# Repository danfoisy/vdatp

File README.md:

# VDATP
## Volumetric Display using an Acoustically Trapped Particle

This was such a fun project - I still giggle (maniacally) when watching this thing go.  There's something truly magical about watching something levitate in mid-air and then start zipping around so fast, you can't see it.  In any case, I hope these project files help someone!

Video: https://www.youtube.com/watch?v=hCC1C5KIeUA

References:
- PhysicsGirl acoustic levitator: https://www.youtube.com/watch?v=ABjRnSYw-4k
- Acoustic levitator Instructable: https://www.instructables.com/Acoustic-Levitator/
- University of Sussex video: https://www.youtube.com/watch?v=Tm8JRlJ1q50
- University of Sussex paper: http://sro.sussex.ac.uk/id/eprint/86930/

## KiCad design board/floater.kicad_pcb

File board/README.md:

# Board

Herein lives the Kicad schedmatics, PCB and BOM files.  If looking to replicate, I highly recommend you look at `errata.txt` for a list of mistakes I made that should be fixed on the next spin of the board.

Some notes:
- SPI goes to all 4 FPGAs simultaneously.  MISO is not used
- there are jumpers in place to allow the board to operate with only one FPGA installed (and only 50 transducers) but to run both FPGAs, the following jumpers must be configured:
-- R122, R123, R124, R126, R127, R128 <= populated
-- R125, R129 <= not populated
-- R105, R111, R113 <= not populated
-- R112 <= populated
- Raspberry Pi W installed on top board only. Top board needs 5V DC/DC converter populated, leave unpopulated on bottom board
-- Rasberry Pi header soldered on backside of Pi 
- U101 and U102 are soldered on top board (note errata on U101). Only U101 populated on bottom board
-- only simple twisted pair required for each RS485 connection
- LEDs only connect on top board (populate LED drivers and connectors)
- each board requires a max of 2A at 24V. No power sequencing required
- to allow the config device to program the FPGAs
-- JP201/JP202 must be left unpopulated
-- JP11001/JP11002 must be cut and msel0/1 must be connected to ground with jumper
- each FPGA must have jumpers configured to tell it which transducers it is responsible for
-- top board: populate R11004
-- bottom board: populate R11003, R203, R204
- original ultrasonic transducer is no available on aliexpress but https://manorshi.en.alibaba.com/product/60248714908-801018150/Manorshi_10mm_40khz_piezo_ultrasonic_Transmitter_Receiver_sensor.html should work but I've not tested (make sure to order the transmitter version)
- distance between boards is not super critical - mine are set up 145mm apart but other distance work just as well
- FPGAs can be programmed with a USB blaster type device.  I use https://www.terasic.com.tw/cgi-bin/page/archive.pl?Language=English&No=46
-- all FPGAs get the same program
- the transducers have a polarity marked on them - but don't trust the markings as they are wrong much of the time.  As well, I've been informed that there are phase discrepancies inherent in most of these cheap transducers.  I corrected for polarity errors by testing each transducer individually but did not correct for phase errors - this may be the cause of some of the distortions I saw.  I did check for these phase discrepancies and found a maximum of about 3% phase error across the transducers.  I don't know if this is enough to cause serious distortions but it may be worthwhile for someone to investigate.  If this is of concern, a simple LUT can be implemented to compensate for these errors on a transducer by transducer basis
- running these boards at 15V causes the drivers to get really hot - I suggest running them at 10V.

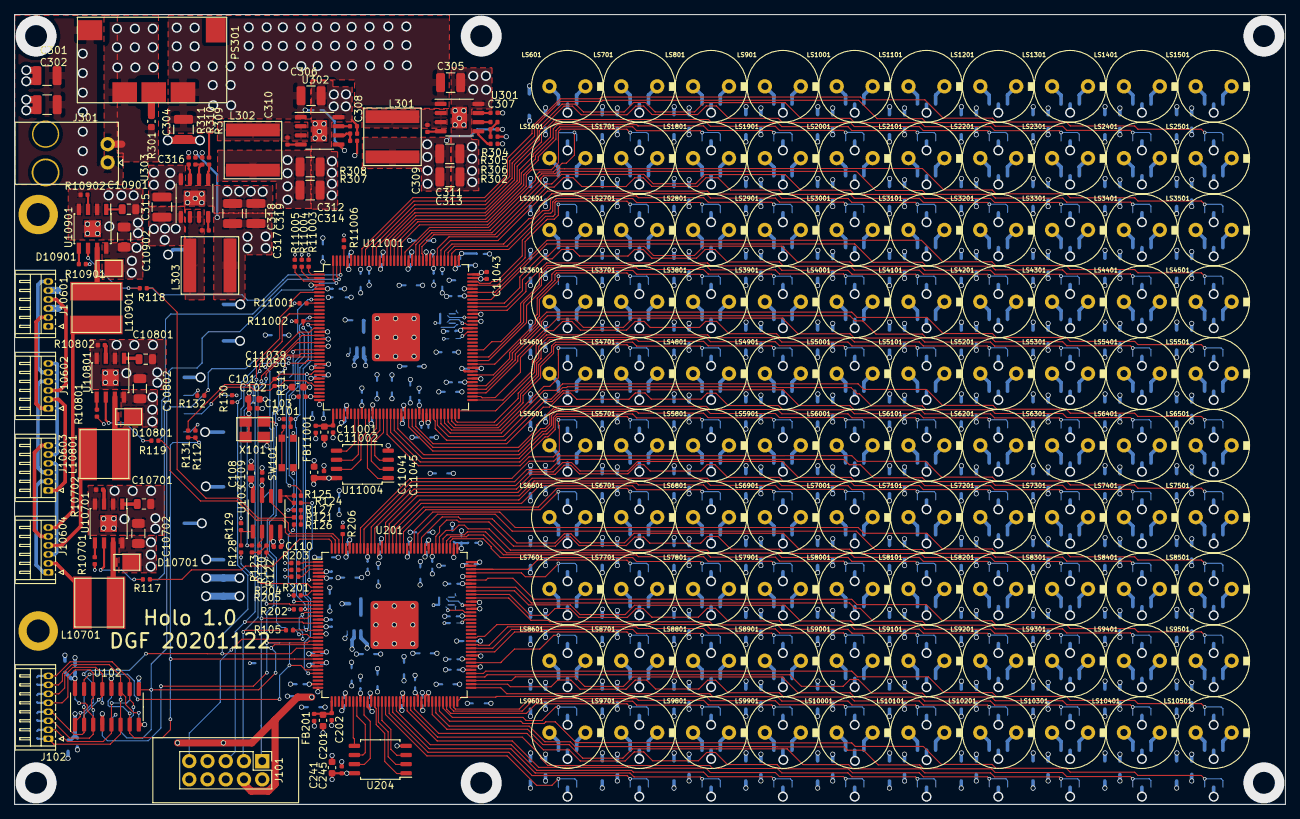
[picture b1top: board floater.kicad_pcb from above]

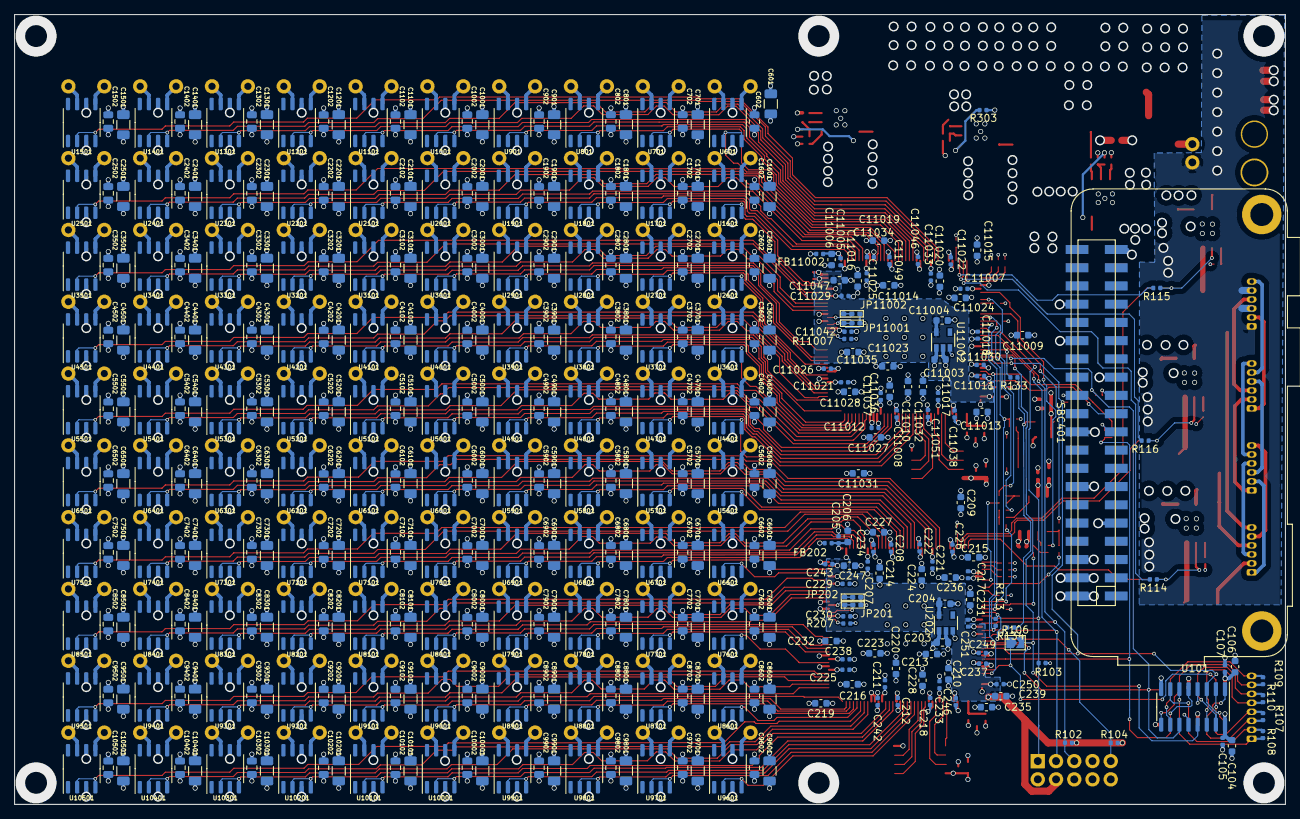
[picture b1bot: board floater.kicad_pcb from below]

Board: 4 copper layers, 177.0 x 110.0 mm, 638 parts (416 on the bottom side), 432 nets.

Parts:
C101, C104, C106, C108, C201, C203, C204, C206, C209, C210, C213, C214, C215, C216, C219, C220, C223, C224, C227, C228, C231, C232, C235, C236, C239, C241, C247, C11001, C11003, C11004, C11006, C11009, C11010, C11013, C11014, C11015, C11016, C11019, C11020, C11023, C11024, C11027, C11028, C11031, C11032, C11035, C11036, C11039, C11041, C11047: 4.7uF; C_0603_1608Metric
C102, C103, C105, C107, C109, C110, C202, C205, C207, C208, C211, C212, C217, C218, C221, C222, C225, C226, C229, C230, C233, C234, C237, C238, C242, C243, C245, C246, C249, C250, C251, C307, C308, C309, C310, C316, C317, C11002, C11005, C11007, C11008, C11011, C11012, C11017, C11018, C11021, C11022, C11025, C11026, C11029, C11030, C11033, C11034, C11037, C11038, C11042, C11043, C11045, C11046, C11049, C11050, C11051: 0.1uF; C_0402_1005Metric
C301, C302: 10uF,50V; R_1210_3225Metric
C304, C305, C306, C315: 22uF,35V; C_1210_3225Metric
C311, C312, C313, C314, C318, C319: 22uF; C_1210_3225Metric
C601, C701, C801, C901, C1001, C1101, C1201, C1301, C1401, C1501, C1601, C1701, C1801, C1901, C2001, C2101, C2201, C2301, C2401, C2501, C2601, C2701, C2801, C2901, C3001, C3101, C3201, C3301, C3401, C3501, C3601, C3701, C3801, C3901, C4001, C4101, C4201, C4301, C4401, C4501, C4601, C4701, C4801, C4901, C5001, C5101, C5201, C5301, C5401, C5501, C5601, C5701, C5801, C5901, C6001, C6101, C6201, C6301, C6401, C6501, C6601, C6701, C6801, C6901, C7001, C7101, C7201, C7301, C7401, C7501, C7601, C7701, C7801, C7901, C8001, C8101, C8201, C8301, C8401, C8501, C8601, C8701, C8801, C8901, C9001, C9101, C9201, C9301, C9401, C9501, C9601, C9701, C9801, C9901, C10001, C10101, C10201, C10301, C10401, C10501, C10702, C10802, C10902: 4.7uF, 35V; C_1206_3216Metric
C602, C702, C802, C902, C1002, C1102, C1202, C1302, C1402, C1502, C1602, C1702, C1802, C1902, C2002, C2102, C2202, C2302, C2402, C2502, C2602, C2702, C2802, C2902, C3002, C3102, C3202, C3302, C3402, C3502, C3602, C3702, C3802, C3902, C4002, C4102, C4202, C4302, C4402, C4502, C4602, C4702, C4802, C4902, C5002, C5102, C5202, C5302, C5402, C5502, C5602, C5702, C5802, C5902, C6002, C6102, C6202, C6302, C6402, C6502, C6602, C6702, C6802, C6902, C7002, C7102, C7202, C7302, C7402, C7502, C7602, C7702, C7802, C7902, C8002, C8102, C8202, C8302, C8402, C8502, C8602, C8702, C8802, C8902, C9002, C9102, C9202, C9302, C9402, C9502, C9602, C9702, C9802, C9902, C10002, C10102, C10202, C10302, C10402, C10502: 0.1uF, 35V; C_0805_2012Metric
C10701, C10801, C10901: 1uF, 16V; C_0805_2012Metric
D10701, D10801, D10901: 2A, 100V; DO-220A
FB201, FB202, FB11001, FB11002: 300R; R_0402_1005Metric
J101: JTAG; PinHeader_2x05_P2.54mm_Vertical_Shrouded
J102: Comms; Hirose_DF13-08P-1.25DS_1x08_P1.25mm_Horizontal
J301: Power; Molex_70555_RA_1x02_P2.54
J10601, J10602, J10603, J10604: Screw_Terminal_01x06; Hirose_DF13-06P-1.25DS_1x06_P1.25mm_Horizontal
JP201, JP202, JP11001, JP11002: SolderJumper_3_Bridged12; SolderJumper-3_bridged12
L301: 2.0uH; NR8040
L302: 3.6uH; NR8040
L303: 4.7uH; NR8040
L10701, L10801, L10901: 11.5uH; SRR6038
LS601, LS701, LS801, LS901, LS1001, LS1101, LS1201, LS1301, LS1401, LS1501, LS1601, LS1701, LS1801, LS1901, LS2001, LS2101, LS2201, LS2301, LS2401, LS2501, LS2601, LS2701, LS2801, LS2901, LS3001, LS3101, LS3201, LS3301, LS3401, LS3501, LS3601, LS3701, LS3801, LS3901, LS4001, LS4101, LS4201, LS4301, LS4401, LS4501, LS4601, LS4701, LS4801, LS4901, LS5001, LS5101, LS5201, LS5301, LS5401, LS5501, LS5601, LS5701, LS5801, LS5901, LS6001, LS6101, LS6201, LS6301, LS6401, LS6501, LS6601, LS6701, LS6801, LS6901, LS7001, LS7101, LS7201, LS7301, LS7401, LS7501, LS7601, LS7701, LS7801, LS7901, LS8001, LS8101, LS8201, LS8301, LS8401, LS8501, LS8601, LS8701, LS8801, LS8901, LS9001, LS9101, LS9201, LS9301, LS9401, LS9501, LS9601, LS9701, LS9801, LS9901, LS10001, LS10101, LS10201, LS10301, LS10401, LS10501: Speaker_Ultrasound; MSO-P1040H07T
PS301: OKI-T36W-W40; OKI-T-36W-W40
R101: 330R; R_0402_1005Metric
R102, R104, R201, R202, R203, R204, R205, R206, R207, R11001, R11002, R11003, R11004, R11005, R11006, R11007: 10K; R_0402_1005Metric
R103: 1.0K; R_0402_1005Metric
R105, R111, R112, R113, R114, R115, R116, R117, R118, R119: 0R; R_0402_1005Metric
R106: 0R; SolderJumper-2_P1.3mm_Open_TrianglePad1.0x1.5mm
R107, R108, R109, R110, R130, R131, R132: 100R; R_0402_1005Metric
R120: 24R9; R_0402_1005Metric
R121: 50R; R_0402_1005Metric
R122, R123, R124, R125, R126, R127, R128, R129: SOT; R_0402_1005Metric
R133, R134: 25R; R_0402_1005Metric
R301: 52R21; R_0603_1608Metric
R302, R303, R309: 100K; R_0402_1005Metric
R304: 47K; R_0402_1005Metric
R305: 5.0K; R_0402_1005Metric
R306: 10.31K; R_0402_1005Metric
R307, R310: 75K; R_0402_1005Metric
R308: 27.6K; R_0402_1005Metric
R311: 14.46K; R_0402_1005Metric
R10701, R10801, R10901: 20K; R_0402_1005Metric
R10702, R10802, R10902: 8.9K; R_0402_1005Metric
SBC401: Raspberry_Pi_2_3; Raspberry_Pi_Zero_Socketed_THT_MountingHoles_SMT
SW101: SW_Push; SW_SPST_KMR2
U101: AM26LV32CDR; SOIC-16_3.9x9.9mm_P1.27mm
U102: AM26LV31; SOIC-16_3.9x9.9mm_P1.27mm
U103: EPCQ16A; SOIC-8_3.9x4.9mm_P1.27mm
U201, U11001: 10CL010YE144C8G; EQFP-144-1EP_20x20mm_P0.5mm_EP6.7x6.7mm
U202, U11002: MIC5504-2.5YM5; SOT-23-5
U204, U11004: S25FL128L; SOIC-8_5.275x5.275mm_P1.27mm
U301, U302, U303: RT7263A; SOP-EP-8_3.9x4.9mm_P1.27mm
U601, U701, U801, U901, U1001, U1101, U1201, U1301, U1401, U1501, U1601, U1701, U1801, U1901, U2001, U2101, U2201, U2301, U2401, U2501, U2601, U2701, U2801, U2901, U3001, U3101, U3201, U3301, U3401, U3501, U3601, U3701, U3801, U3901, U4001, U4101, U4201, U4301, U4401, U4501, U4601, U4701, U4801, U4901, U5001, U5101, U5201, U5301, U5401, U5501, U5601, U5701, U5801, U5901, U6001, U6101, U6201, U6301, U6401, U6501, U6601, U6701, U6801, U6901, U7001, U7101, U7201, U7301, U7401, U7501, U7601, U7701, U7801, U7901, U8001, U8101, U8201, U8301, U8401, U8501, U8601, U8701, U8801, U8901, U9001, U9101, U9201, U9301, U9401, U9501, U9601, U9701, U9801, U9901, U10001, U10101, U10201, U10301, U10401, U10501: TC4428A; SO-8_3.9x4.9mm_P1.27mm
U10701, U10801, U10901: LM3414HV; SOIC-8-1EP_3.9x4.9mm_P1.27mm_EP2.35x2.35mm
X101: ASE-24.576MHz; ASFL1

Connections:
+1V2: C207.1, C210.1, C211.1, C214.1, C216.1, C217.1, C220.1, C221.1, C224.1, C225.1, C228.1, C229.1, C232.1, C233.1, C236.1, C237.1, C311.1, C313.1, C11007.1, C11010.1, C11011.1, C11014.1, C11016.1, C11017.1, C11020.1, C11021.1, C11024.1, C11025.1, C11028.1, C11029.1, C11032.1, C11033.1, C11036.1, C11037.1, FB201.1, FB202.1, FB11001.1, FB11002.1, L301.2, R305.1, U201.5, U201.29, U201.45, U201.61, U201.78, U201.102, U201.116, U201.134, U11001.5, U11001.29, U11001.45, U11001.61, U11001.78, U11001.102, U11001.116, U11001.134
+2V5: C204.1, C239.1, C243.1, C247.1, C250.1, J101.4, JP201.1, JP202.1, R102.2, R104.2, U201.35, U201.107, U202.5
+3V0: C101.1, C102.1, C104.1, C105.1, C106.1, C107.1, C108.1, C109.1, C110.1, C203.1, C208.1, C209.1, C212.1, C213.1, C215.1, C218.1, C219.1, C222.1, C223.1, C226.1, C227.1, C230.1, C231.1, C234.1, C235.1, C238.1, C241.1, C242.1, C245.1, C246.1, C249.1, C251.1, C312.1, C314.1, C11003.1, C11008.1, C11009.1, C11012.1, C11013.1, C11015.1, C11018.1, C11019.1, C11022.1, C11023.1, C11026.1, C11027.1, C11030.1, C11031.1, C11034.1, C11035.1, C11038.1, C11041.1, C11042.1, C11045.1, C11046.1, C11049.1, C11051.1, L302.2, R201.2, R202.2, R207.2, R307.1, R11001.2, R11002.2, R11007.2, U101.4, U101.16, U102.4, U102.16, U103.3, U103.7, U103.8, U201.17, U201.26, U201.40, U201.47, U201.56, U201.62, U201.81, U201.93, U201.117, U201.122, U201.130, U201.139, U202.1, U202.3, U204.8, U11001.17, U11001.26, U11001.40, U11001.47, U11001.56, U11001.62, U11001.81, U11001.93, U11001.117, U11001.122, U11001.130, U11001.139, U11002.1, U11002.3, U11004.8, X101.1, X101.4
+5V: C318.1, C319.1, L303.2, R310.1, SBC401.2, SBC401.4
+15V: C304.1, C305.1, C306.1, C315.1, C601.1, C602.1, C701.1, C702.1, C801.1, C802.1, C901.1, C902.1, C1001.1, C1002.1, C1101.1, C1102.1, C1201.1, C1202.1, C1301.1, C1302.1, C1401.1, C1402.1, C1501.1, C1502.1, C1601.1, C1602.1, C1701.1, C1702.1, C1801.1, C1802.1, C1901.1, C1902.1, C2001.1, C2002.1, C2101.1, C2102.1, C2201.1, C2202.1, C2301.1, C2302.1, C2401.1, C2402.1, C2501.1, C2502.1, C2601.1, C2602.1, C2701.1, C2702.1, C2801.1, C2802.1, C2901.1, C2902.1, C3001.1, C3002.1, C3101.1, C3102.1, C3201.1, C3202.1, C3301.1, C3302.1, C3401.1, C3402.1, C3501.1, C3502.1, C3601.1, C3602.1, C3701.1, C3702.1, C3801.1, C3802.1, C3901.1, C3902.1, C4001.1, C4002.1, C4101.1, C4102.1, C4201.1, C4202.1, C4301.1, C4302.1, C4401.1, C4402.1, C4501.1, C4502.1, C4601.1, C4602.1, C4701.1, C4702.1, C4801.1, C4802.1, C4901.1, C4902.1, C5001.1, C5002.1, C5101.1, C5102.1, C5201.1, C5202.1, C5301.1, C5302.1, C5401.1, C5402.1, C5501.1, C5502.1, C5601.1, C5602.1, C5701.1, C5702.1, C5801.1, C5802.1, C5901.1, C5902.1, C6001.1, C6002.1, C6101.1, C6102.1, C6201.1, C6202.1, C6301.1, C6302.1, C6401.1, C6402.1, C6501.1, C6502.1, C6601.1, C6602.1, C6701.1, C6702.1, C6801.1, C6802.1, C6901.1, C6902.1, C7001.1, C7002.1, C7101.1, C7102.1, C7201.1, C7202.1, C7301.1, C7302.1, C7401.1, C7402.1, C7501.1, C7502.1, C7601.1, C7602.1, C7701.1, C7702.1, C7801.1, C7802.1, C7901.1, C7902.1, C8001.1, C8002.1, C8101.1, C8102.1, C8201.1, C8202.1, C8301.1, C8302.1, C8401.1, C8402.1, C8501.1, C8502.1, C8601.1, C8602.1, C8701.1, C8702.1, C8801.1, C8802.1, C8901.1, C8902.1, C9001.1, C9002.1, C9101.1, C9102.1, C9201.1, C9202.1, C9301.1, C9302.1, C9401.1, C9402.1, C9501.1, C9502.1, C9601.1, C9602.1, C9701.1, C9702.1, C9801.1, C9802.1, C9901.1, C9902.1, C10001.1, C10002.1, C10101.1, C10102.1, C10201.1, C10202.1, C10301.1, C10302.1, C10401.1, C10402.1, C10501.1, C10502.1, PS301.5, R302.1, R303.1, R309.1, U301.1, U302.1, U303.1, U601.6, U701.6, U801.6, U901.6, U1001.6, U1101.6, U1201.6, U1301.6, U1401.6, U1501.6, U1601.6, U1701.6, U1801.6, U1901.6, U2001.6, U2101.6, U2201.6, U2301.6, U2401.6, U2501.6, U2601.6, U2701.6, U2801.6, U2901.6, U3001.6, U3101.6, U3201.6, U3301.6, U3401.6, U3501.6, U3601.6, U3701.6, U3801.6, U3901.6, U4001.6, U4101.6, U4201.6, U4301.6, U4401.6, U4501.6, U4601.6, U4701.6, U4801.6, U4901.6, U5001.6, U5101.6, U5201.6, U5301.6, U5401.6, U5501.6, U5601.6, U5701.6, U5801.6, U5901.6, U6001.6, U6101.6, U6201.6, U6301.6, U6401.6, U6501.6, U6601.6, U6701.6, U6801.6, U6901.6, U7001.6, U7101.6, U7201.6, U7301.6, U7401.6, U7501.6, U7601.6, U7701.6, U7801.6, U7901.6, U8001.6, U8101.6, U8201.6, U8301.6, U8401.6, U8501.6, U8601.6, U8701.6, U8801.6, U8901.6, U9001.6, U9101.6, U9201.6, U9301.6, U9401.6, U9501.6, U9601.6, U9701.6, U9801.6, U9901.6, U10001.6, U10101.6, U10201.6, U10301.6, U10401.6, U10501.6
+VSW: C301.1, C302.1, C10702.1, C10802.1, C10902.1, D10701.1, D10801.1, D10901.1, J301.1, J10601.1, J10601.3, J10601.5, PS301.2, U10701.8, U10801.8, U10901.8
/1A: J102.4, R107.1, U101.2, U102.2
/1B: J102.3, R107.2, U101.1, U102.3
/2A: J102.1, R108.1, U101.6, U102.6
/2B: J102.2, R108.2, U101.7, U102.5
/3A: J102.8, R109.1, U101.10, U102.10
/3B: J102.7, R109.2, U101.9, U102.11
/4A: J102.5, R110.1, U101.14, U102.14
/4B: J102.6, R110.2, U101.15, U102.13
/FPGA1/CLK24_576: R134.2, U201.22
/FPGA1/blue: R118.2, U201.142
/FPGA1/f_io0: U201.43, U204.5
/FPGA1/f_io1: U201.50, U204.2
/FPGA1/f_io2: U201.51, U204.3
/FPGA1/f_io3: U201.46, U204.7
/FPGA1/f_ncs: U201.49, U204.1
/FPGA1/f_sck: U201.44, U204.6
/FPGA1/green: R119.2, U201.143
/FPGA1/left: R204.2, U201.2
/FPGA1/misc0: R205.2, U201.3
/FPGA1/misc1: R206.2, U201.141
/FPGA1/miso: R111.1, R112.1, U201.32, U11001.28
/FPGA1/msel0: JP201.2, U201.94
/FPGA1/msel1: JP202.2, U201.96
/FPGA1/red: R117.2, U201.144
/FPGA1/top: R203.2, U201.1
/FPGA2/+2.5V: C11004.1, C11039.1, C11043.1, C11047.1, C11050.1, JP11001.1, JP11002.1, U11001.35, U11001.107, U11002.5
/FPGA2/CLK24_576: R133.2, U11001.22
/FPGA2/blue: R115.2, U11001.142
/FPGA2/f_io0: U11001.43, U11004.5
/FPGA2/f_io1: U11001.50, U11004.2
/FPGA2/f_io2: U11001.51, U11004.3
/FPGA2/f_io3: U11001.46, U11004.7
/FPGA2/f_ncs: U11001.49, U11004.1
/FPGA2/f_sck: U11001.44, U11004.6
/FPGA2/green: R116.2, U11001.143
/FPGA2/left: R11004.2, U11001.2
/FPGA2/misc0: R11005.2, U11001.3
/FPGA2/misc1: R11006.2, U11001.141
/FPGA2/msel0: JP11001.2, U11001.94
/FPGA2/msel1: JP11002.2, U11001.96
/FPGA2/red: R114.2, U11001.144
/FPGA2/t0: U4601.2, U4601.4, U11001.52
/FPGA2/t1: U4701.2, U4701.4, U11001.53
/FPGA2/t2: U4801.2, U4801.4, U11001.54
/FPGA2/t3: U4901.2, U4901.4, U11001.55
/FPGA2/t4: U5001.2, U5001.4, U11001.58
/FPGA2/t5: U5101.2, U5101.4, U11001.59
/FPGA2/t6: U5201.2, U5201.4, U11001.60
/FPGA2/t7: U5301.2, U5301.4, U11001.65
/FPGA2/t8: U5401.2, U5401.4, U11001.66
/FPGA2/t9: U5501.2, U5501.4, U11001.67
/FPGA2/t10: U3601.2, U3601.4, U11001.68
/FPGA2/t11: U3701.2, U3701.4, U11001.69
/FPGA2/t12: U3801.2, U3801.4, U11001.70
/FPGA2/t13: U3901.2, U3901.4, U11001.71
/FPGA2/t14: U4001.2, U4001.4, U11001.72
/FPGA2/t15: U4101.2, U4101.4, U11001.73
/FPGA2/t16: U4201.2, U4201.4, U11001.74
/FPGA2/t17: U4301.2, U4301.4, U11001.75
/FPGA2/t18: U4401.2, U4401.4, U11001.76
/FPGA2/t19: U4501.2, U4501.4, U11001.77
/FPGA2/t20: U2601.2, U2601.4, U11001.80
/FPGA2/t21: U2701.2, U2701.4, U11001.83
/FPGA2/t22: U2801.2, U2801.4, U11001.84
/FPGA2/t23: U2901.2, U2901.4, U11001.85
/FPGA2/t24: U3001.2, U3001.4, U11001.87
/FPGA2/t25: U3101.2, U3101.4, U11001.98
/FPGA2/t26: U3201.2, U3201.4, U11001.99
/FPGA2/t27: U3301.2, U3301.4, U11001.100
/FPGA2/t28: U3401.2, U3401.4, U11001.101
/FPGA2/t29: U3501.2, U3501.4, U11001.103
/FPGA2/t30: U1601.2, U1601.4, U11001.105
/FPGA2/t31: U1701.2, U1701.4, U11001.106
/FPGA2/t32: U1801.2, U1801.4, U11001.111
/FPGA2/t33: U1901.2, U1901.4, U11001.112
/FPGA2/t34: U2001.2, U2001.4, U11001.113
/FPGA2/t35: U2101.2, U2101.4, U11001.114
/FPGA2/t36: U2201.2, U2201.4, U11001.115
/FPGA2/t37: U2301.2, U2301.4, U11001.119
/FPGA2/t38: U2401.2, U2401.4, U11001.120
/FPGA2/t39: U2501.2, U2501.4, U11001.121
/FPGA2/t40: U601.2, U601.4, U11001.124
/FPGA2/t41: U701.2, U701.4, U11001.125
/FPGA2/t42: U801.2, U801.4, U11001.126
/FPGA2/t43: U901.2, U901.4, U11001.127
/FPGA2/t44: U1001.2, U1001.4, U11001.128
/FPGA2/t45: U1101.2, U1101.4, U11001.129
/FPGA2/t46: U1201.2, U1201.4, U11001.132
/FPGA2/t47: U1301.2, U1301.4, U11001.133
/FPGA2/t48: U1401.2, U1401.4, U11001.135
/FPGA2/t49: U1501.2, U1501.4, U11001.136
/FPGA2/tdi: R105.1, R113.1, U201.20, U11001.15
/FPGA2/top: R11003.2, U11001.1
/LED/LED driver/LED_cath: J10604.2, L10701.2
/LED/sheet5F55454A/LED_cath: J10604.4, L10801.2
/LED/sheet5F55462D/LED_cath: J10604.6, L10901.2
/Raspberry PI/mosi: R131.2, SBC401.19
/Raspberry PI/nCE0: R130.2, SBC401.24
/Raspberry PI/sclk: R132.2, SBC401.23
/Transducers/s0: U201.52, U9601.2, U9601.4
/Transducers/s1: U201.53, U9701.2, U9701.4
/Transducers/s2: U201.54, U9801.2, U9801.4
/Transducers/s3: U201.55, U9901.2, U9901.4
/Transducers/s4: U201.58, U10001.2, U10001.4
/Transducers/s5: U201.59, U10101.2, U10101.4
/Transducers/s6: U201.60, U10201.2, U10201.4
/Transducers/s7: U201.65, U10301.2, U10301.4
/Transducers/s8: U201.66, U10401.2, U10401.4
/Transducers/s9: U201.67, U10501.2, U10501.4
/Transducers/s10: U201.68, U8601.2, U8601.4
/Transducers/s11: U201.69, U8701.2, U8701.4
/Transducers/s12: U201.70, U8801.2, U8801.4
/Transducers/s13: U201.71, U8901.2, U8901.4
/Transducers/s14: U201.72, U9001.2, U9001.4
/Transducers/s15: U201.73, U9101.2, U9101.4
/Transducers/s16: U201.74, U9201.2, U9201.4
/Transducers/s17: U201.75, U9301.2, U9301.4
/Transducers/s18: U201.76, U9401.2, U9401.4
/Transducers/s19: U201.77, U9501.2, U9501.4
/Transducers/s20: U201.80, U7601.2, U7601.4
/Transducers/s21: U201.83, U7701.2, U7701.4
/Transducers/s22: U201.84, U7801.2, U7801.4
/Transducers/s23: U201.85, U7901.2, U7901.4
/Transducers/s24: U201.87, U8001.2, U8001.4
/Transducers/s25: U201.98, U8101.2, U8101.4
/Transducers/s26: U201.99, U8201.2, U8201.4
/Transducers/s27: U201.100, U8301.2, U8301.4
/Transducers/s28: U201.101, U8401.2, U8401.4
/Transducers/s29: U201.103, U8501.2, U8501.4
/Transducers/s30: U201.105, U6601.2, U6601.4
/Transducers/s31: U201.106, U6701.2, U6701.4
/Transducers/s32: U201.111, U6801.2, U6801.4
/Transducers/s33: U201.112, U6901.2, U6901.4
/Transducers/s34: U201.113, U7001.2, U7001.4
/Transducers/s35: U201.114, U7101.2, U7101.4
/Transducers/s36: U201.115, U7201.2, U7201.4
/Transducers/s37: U201.119, U7301.2, U7301.4
/Transducers/s38: U201.120, U7401.2, U7401.4
/Transducers/s39: U201.121, U7501.2, U7501.4
/Transducers/s40: U201.124, U5601.2, U5601.4
/Transducers/s41: U201.125, U5701.2, U5701.4
/Transducers/s42: U201.126, U5801.2, U5801.4
/Transducers/s43: U201.127, U5901.2, U5901.4
/Transducers/s44: U201.128, U6001.2, U6001.4
/Transducers/s45: U201.129, U6101.2, U6101.4
/Transducers/s46: U201.132, U6201.2, U6201.4
/Transducers/s47: U201.133, U6301.2, U6301.4
/Transducers/s48: U201.135, U6401.2, U6401.4
/Transducers/s49: U201.136, U6501.2, U6501.4
/as_asdo_1: R124.2, U201.6
/as_asdo_2: R125.2, U11001.8
/as_data0_1: R122.2, U201.13
/as_data0_2: R123.2, U11001.6
/as_dclk_1: R126.2, U201.12
/as_dclk_2: R127.2, U11001.13
/as_ncs_1: R128.2, U201.8
/as_ncs_2: R129.2, U11001.12
/blueDim: R115.1, R118.1, U10901.6
/clk: R133.1, R134.1, X101.3
/greenDim: R116.1, R119.1, U10801.6
/miso: R111.2, SBC401.21, U11001.32
/mosi: R112.2, R131.1, U101.5, U102.7, U201.28
/nConfig: C103.1, R101.2, R202.1, R11002.1, U201.14, U11001.14
/ncs: R130.1, U101.3, U102.1, U201.25, U11001.25
/redDim: R114.1, R117.1, U10701.6
/sck: R132.1, U101.11, U102.9, U201.24, U11001.24
/syncIn: R106.2, U101.13, U201.23, U11001.23
/syncOut: R106.1, U102.15, U201.31
/tck: J101.1, R103.2, U201.16, U11001.16
/tdi: J101.9, R104.1, R113.2, U201.15
/tdo: J101.3, R105.2, U11001.20
/tms: J101.5, R102.1, U201.18, U11001.18
GND: C101.2, C102.2, C103.2, C104.2, C105.2, C106.2, C107.2, C108.2, C109.2, C110.2, C201.2, C202.2, C203.2, C204.2, C205.2, C206.2, C207.2, C208.2, C209.2, C210.2, C211.2, C212.2, C213.2, C214.2, C215.2, C216.2, C217.2, C218.2, C219.2, C220.2, C221.2, C222.2, C223.2, C224.2, C225.2, C226.2, C227.2, C228.2, C229.2, C230.2, C231.2, C232.2, C233.2, C234.2, C235.2, C236.2, C237.2, C238.2, C239.2, C241.2, C242.2, C243.2, C245.2, C246.2, C247.2, C249.2, C250.2, C251.2, C301.2, C302.2, C304.2, C305.2, C306.2, C307.2, C308.2, C311.2, C312.2, C313.2, C314.2, C315.2, C316.2, C318.2, C319.2, C601.2, C602.2, C701.2, C702.2, C801.2, C802.2, C901.2, C902.2, C1001.2, C1002.2, C1101.2, C1102.2, C1201.2, C1202.2, C1301.2, C1302.2, C1401.2, C1402.2, C1501.2, C1502.2, C1601.2, C1602.2, C1701.2, C1702.2, C1801.2, C1802.2, C1901.2, C1902.2, C2001.2, C2002.2, C2101.2, C2102.2, C2201.2, C2202.2, C2301.2, C2302.2, C2401.2, C2402.2, C2501.2, C2502.2, C2601.2, C2602.2, C2701.2, C2702.2, C2801.2, C2802.2, C2901.2, C2902.2, C3001.2, C3002.2, C3101.2, C3102.2, C3201.2, C3202.2, C3301.2, C3302.2, C3401.2, C3402.2, C3501.2, C3502.2, C3601.2, C3602.2, C3701.2, C3702.2, C3801.2, C3802.2, C3901.2, C3902.2, C4001.2, C4002.2, C4101.2, C4102.2, C4201.2, C4202.2, C4301.2, C4302.2, C4401.2, C4402.2, C4501.2, C4502.2, C4601.2, C4602.2, C4701.2, C4702.2, C4801.2, C4802.2, C4901.2, C4902.2, C5001.2, C5002.2, C5101.2, C5102.2, C5201.2, C5202.2, C5301.2, C5302.2, C5401.2, C5402.2, C5501.2, C5502.2, C5601.2, C5602.2, C5701.2, C5702.2, C5801.2, C5802.2, C5901.2, C5902.2, C6001.2, C6002.2, C6101.2, C6102.2, C6201.2, C6202.2, C6301.2, C6302.2, C6401.2, C6402.2, C6501.2, C6502.2, C6601.2, C6602.2, C6701.2, C6702.2, C6801.2, C6802.2, C6901.2, C6902.2, C7001.2, C7002.2, C7101.2, C7102.2, C7201.2, C7202.2, C7301.2, C7302.2, C7401.2, C7402.2, C7501.2, C7502.2, C7601.2, C7602.2, C7701.2, C7702.2, C7801.2, C7802.2, C7901.2, C7902.2, C8001.2, C8002.2, C8101.2, C8102.2, C8201.2, C8202.2, C8301.2, C8302.2, C8401.2, C8402.2, C8501.2, C8502.2, C8601.2, C8602.2, C8701.2, C8702.2, C8801.2, C8802.2, C8901.2, C8902.2, C9001.2, C9002.2, C9101.2, C9102.2, C9201.2, C9202.2, C9301.2, C9302.2, C9401.2, C9402.2, C9501.2, C9502.2, C9601.2, C9602.2, C9701.2, C9702.2, C9801.2, C9802.2, C9901.2, C9902.2, C10001.2, C10002.2, C10101.2, C10102.2, C10201.2, C10202.2, C10301.2, C10302.2, C10401.2, C10402.2, C10501.2, C10502.2, C10701.2, C10702.2, C10801.2, C10802.2, C10901.2, C10902.2, C11001.2, C11002.2, C11003.2, C11004.2, C11005.2, C11006.2, C11007.2, C11008.2, C11009.2, C11010.2, C11011.2, C11012.2, C11013.2, C11014.2, C11015.2, C11016.2, C11017.2, C11018.2, C11019.2, C11020.2, C11021.2, C11022.2, C11023.2, C11024.2, C11025.2, C11026.2, C11027.2, C11028.2, C11029.2, C11030.2, C11031.2, C11032.2, C11033.2, C11034.2, C11035.2, C11036.2, C11037.2, C11038.2, C11039.2, C11041.2, C11042.2, C11043.2, C11045.2, C11046.2, C11047.2, C11049.2, C11050.2, C11051.2, J101.2, J101.10, J301.2, JP201.3, JP202.3, JP11001.3, JP11002.3, PS301.3, R103.1, R203.1, R204.1, R205.1, R206.1, R301.2, R306.2, R308.2, R311.2, R10701.1, R10702.2, R10801.1, R10802.2, R10901.1, R10902.2, R11003.1, R11004.1, R11005.1, R11006.1, SBC401.6, SBC401.9, SBC401.14, SBC401.20, SBC401.25, SBC401.30, SBC401.34, SBC401.39, SW101.1, U101.8, U101.12, U102.8, U102.12, U103.4, U201.4, U201.19, U201.21, U201.27, U201.30, U201.36, U201.41, U201.48, U201.57, U201.63, U201.64, U201.79, U201.82, U201.95, U201.97, U201.104, U201.108, U201.110, U201.118, U201.123, U201.131, U201.140, U201.145, U202.2, U204.4, U301.8, U301.9, U302.8, U302.9, U303.8, U303.9, U601.3, U701.3, U801.3, U901.3, U1001.3, U1101.3, U1201.3, U1301.3, U1401.3, U1501.3, U1601.3, U1701.3, U1801.3, U1901.3, U2001.3, U2101.3, U2201.3, U2301.3, U2401.3, U2501.3, U2601.3, U2701.3, U2801.3, U2901.3, U3001.3, U3101.3, U3201.3, U3301.3, U3401.3, U3501.3, U3601.3, U3701.3, U3801.3, U3901.3, U4001.3, U4101.3, U4201.3, U4301.3, U4401.3, U4501.3, U4601.3, U4701.3, U4801.3, U4901.3, U5001.3, U5101.3, U5201.3, U5301.3, U5401.3, U5501.3, U5601.3, U5701.3, U5801.3, U5901.3, U6001.3, U6101.3, U6201.3, U6301.3, U6401.3, U6501.3, U6601.3, U6701.3, U6801.3, U6901.3, U7001.3, U7101.3, U7201.3, U7301.3, U7401.3, U7501.3, U7601.3, U7701.3, U7801.3, U7901.3, U8001.3, U8101.3, U8201.3, U8301.3, U8401.3, U8501.3, U8601.3, U8701.3, U8801.3, U8901.3, U9001.3, U9101.3, U9201.3, U9301.3, U9401.3, U9501.3, U9601.3, U9701.3, U9801.3, U9901.3, U10001.3, U10101.3, U10201.3, U10301.3, U10401.3, U10501.3, U10701.2, U10701.4, U10701.9, U10801.2, U10801.4, U10801.9, U10901.2, U10901.4, U10901.9, U11001.4, U11001.19, U11001.21, U11001.27, U11001.30, U11001.36, U11001.41, U11001.48, U11001.57, U11001.63, U11001.64, U11001.79, U11001.82, U11001.95, U11001.97, U11001.104, U11001.108, U11001.110, U11001.118, U11001.123, U11001.131, U11001.140, U11001.145, U11002.2, U11004.4, X101.2
unnamed: C201.1, C202.1, FB201.2, U201.37
unnamed: C205.1, C206.1, FB202.2, U201.109
unnamed: C307.1, U301.7
unnamed: C308.1, U302.7
unnamed: C309.1, U301.4
unnamed: C309.2, L301.1, U301.2, U301.3
unnamed: C310.1, U302.4
unnamed: C310.2, L302.1, U302.2, U302.3
unnamed: C316.1, U303.7
unnamed: C317.1, U303.4
unnamed: C317.2, L303.1, U303.2, U303.3
unnamed: C10701.1, U10701.1
unnamed: C10801.1, U10801.1
unnamed: C10901.1, U10901.1
unnamed: C11001.1, C11002.1, FB11001.2, U11001.37
unnamed: C11005.1, C11006.1, FB11002.2, U11001.109
unnamed: D10701.2, L10701.1, U10701.7
unnamed: D10801.2, L10801.1, U10801.7
unnamed: D10901.2, L10901.1, U10901.7
unnamed: J10601.2, J10602.1
unnamed: J10601.4, J10602.3
unnamed: J10601.6, J10602.5
unnamed: J10602.2, J10603.1
unnamed: J10602.4, J10603.3
unnamed: J10602.6, J10603.5
unnamed: J10603.2, J10604.1
unnamed: J10603.4, J10604.3
unnamed: J10603.6, J10604.5
unnamed: LS601.1, U601.7
unnamed: LS601.2, U601.5
unnamed: LS701.1, U701.7
unnamed: LS701.2, U701.5
unnamed: LS801.1, U801.7
unnamed: LS801.2, U801.5
unnamed: LS901.1, U901.7
unnamed: LS901.2, U901.5
unnamed: LS1001.1, U1001.7
unnamed: LS1001.2, U1001.5
unnamed: LS1101.1, U1101.7
unnamed: LS1101.2, U1101.5
unnamed: LS1201.1, U1201.7
unnamed: LS1201.2, U1201.5
unnamed: LS1301.1, U1301.7
unnamed: LS1301.2, U1301.5
unnamed: LS1401.1, U1401.7
unnamed: LS1401.2, U1401.5
unnamed: LS1501.1, U1501.7
unnamed: LS1501.2, U1501.5
unnamed: LS1601.1, U1601.7
unnamed: LS1601.2, U1601.5
unnamed: LS1701.1, U1701.7
unnamed: LS1701.2, U1701.5
unnamed: LS1801.1, U1801.7
unnamed: LS1801.2, U1801.5
unnamed: LS1901.1, U1901.7
unnamed: LS1901.2, U1901.5
unnamed: LS2001.1, U2001.7
unnamed: LS2001.2, U2001.5
unnamed: LS2101.1, U2101.7
unnamed: LS2101.2, U2101.5
unnamed: LS2201.1, U2201.7
unnamed: LS2201.2, U2201.5
unnamed: LS2301.1, U2301.7
unnamed: LS2301.2, U2301.5
unnamed: LS2401.1, U2401.7
unnamed: LS2401.2, U2401.5
unnamed: LS2501.1, U2501.7
unnamed: LS2501.2, U2501.5
unnamed: LS2601.1, U2601.7
unnamed: LS2601.2, U2601.5
unnamed: LS2701.1, U2701.7
unnamed: LS2701.2, U2701.5
unnamed: LS2801.1, U2801.7
unnamed: LS2801.2, U2801.5
unnamed: LS2901.1, U2901.7
unnamed: LS2901.2, U2901.5
unnamed: LS3001.1, U3001.7
unnamed: LS3001.2, U3001.5
unnamed: LS3101.1, U3101.7
unnamed: LS3101.2, U3101.5
unnamed: LS3201.1, U3201.7
unnamed: LS3201.2, U3201.5
unnamed: LS3301.1, U3301.7
unnamed: LS3301.2, U3301.5
unnamed: LS3401.1, U3401.7
unnamed: LS3401.2, U3401.5
unnamed: LS3501.1, U3501.7
unnamed: LS3501.2, U3501.5
unnamed: LS3601.1, U3601.7
unnamed: LS3601.2, U3601.5
unnamed: LS3701.1, U3701.7
unnamed: LS3701.2, U3701.5
unnamed: LS3801.1, U3801.7
unnamed: LS3801.2, U3801.5
unnamed: LS3901.1, U3901.7
unnamed: LS3901.2, U3901.5
unnamed: LS4001.1, U4001.7
unnamed: LS4001.2, U4001.5
unnamed: LS4101.1, U4101.7
unnamed: LS4101.2, U4101.5
unnamed: LS4201.1, U4201.7
unnamed: LS4201.2, U4201.5
unnamed: LS4301.1, U4301.7
unnamed: LS4301.2, U4301.5
unnamed: LS4401.1, U4401.7
unnamed: LS4401.2, U4401.5
unnamed: LS4501.1, U4501.7
unnamed: LS4501.2, U4501.5
unnamed: LS4601.1, U4601.7
unnamed: LS4601.2, U4601.5
unnamed: LS4701.1, U4701.7
unnamed: LS4701.2, U4701.5
unnamed: LS4801.1, U4801.7
unnamed: LS4801.2, U4801.5
unnamed: LS4901.1, U4901.7
unnamed: LS4901.2, U4901.5
unnamed: LS5001.1, U5001.7
unnamed: LS5001.2, U5001.5
unnamed: LS5101.1, U5101.7
unnamed: LS5101.2, U5101.5
unnamed: LS5201.1, U5201.7
unnamed: LS5201.2, U5201.5
unnamed: LS5301.1, U5301.7
unnamed: LS5301.2, U5301.5
unnamed: LS5401.1, U5401.7
unnamed: LS5401.2, U5401.5
unnamed: LS5501.1, U5501.7
unnamed: LS5501.2, U5501.5
unnamed: LS5601.1, U5601.7
unnamed: LS5601.2, U5601.5
unnamed: LS5701.1, U5701.7
unnamed: LS5701.2, U5701.5
unnamed: LS5801.1, U5801.7
unnamed: LS5801.2, U5801.5
unnamed: LS5901.1, U5901.7
unnamed: LS5901.2, U5901.5
unnamed: LS6001.1, U6001.7
unnamed: LS6001.2, U6001.5
unnamed: LS6101.1, U6101.7
unnamed: LS6101.2, U6101.5
unnamed: LS6201.1, U6201.7
unnamed: LS6201.2, U6201.5
unnamed: LS6301.1, U6301.7
unnamed: LS6301.2, U6301.5
unnamed: LS6401.1, U6401.7
unnamed: LS6401.2, U6401.5
unnamed: LS6501.1, U6501.7
unnamed: LS6501.2, U6501.5
unnamed: LS6601.1, U6601.7
unnamed: LS6601.2, U6601.5
unnamed: LS6701.1, U6701.7
unnamed: LS6701.2, U6701.5
unnamed: LS6801.1, U6801.7
unnamed: LS6801.2, U6801.5
unnamed: LS6901.1, U6901.7
unnamed: LS6901.2, U6901.5
unnamed: LS7001.1, U7001.7
unnamed: LS7001.2, U7001.5
unnamed: LS7101.1, U7101.7
unnamed: LS7101.2, U7101.5
unnamed: LS7201.1, U7201.7
unnamed: LS7201.2, U7201.5
unnamed: LS7301.1, U7301.7
unnamed: LS7301.2, U7301.5
unnamed: LS7401.1, U7401.7
unnamed: LS7401.2, U7401.5
unnamed: LS7501.1, U7501.7
unnamed: LS7501.2, U7501.5
unnamed: LS7601.1, U7601.7
unnamed: LS7601.2, U7601.5
unnamed: LS7701.1, U7701.7
unnamed: LS7701.2, U7701.5
unnamed: LS7801.1, U7801.7
unnamed: LS7801.2, U7801.5
unnamed: LS7901.1, U7901.7
unnamed: LS7901.2, U7901.5
unnamed: LS8001.1, U8001.7
unnamed: LS8001.2, U8001.5
unnamed: LS8101.1, U8101.7
unnamed: LS8101.2, U8101.5
unnamed: LS8201.1, U8201.7
unnamed: LS8201.2, U8201.5
unnamed: LS8301.1, U8301.7
unnamed: LS8301.2, U8301.5
unnamed: LS8401.1, U8401.7
unnamed: LS8401.2, U8401.5
unnamed: LS8501.1, U8501.7
unnamed: LS8501.2, U8501.5
unnamed: LS8601.1, U8601.7
unnamed: LS8601.2, U8601.5
unnamed: LS8701.1, U8701.7
unnamed: LS8701.2, U8701.5
unnamed: LS8801.1, U8801.7
unnamed: LS8801.2, U8801.5
unnamed: LS8901.1, U8901.7
unnamed: LS8901.2, U8901.5
unnamed: LS9001.1, U9001.7
unnamed: LS9001.2, U9001.5
unnamed: LS9101.1, U9101.7
unnamed: LS9101.2, U9101.5
unnamed: LS9201.1, U9201.7
unnamed: LS9201.2, U9201.5
unnamed: LS9301.1, U9301.7
unnamed: LS9301.2, U9301.5
unnamed: LS9401.1, U9401.7
unnamed: LS9401.2, U9401.5
unnamed: LS9501.1, U9501.7
unnamed: LS9501.2, U9501.5
unnamed: LS9601.1, U9601.7
unnamed: LS9601.2, U9601.5
unnamed: LS9701.1, U9701.7
unnamed: LS9701.2, U9701.5
unnamed: LS9801.1, U9801.7
unnamed: LS9801.2, U9801.5
unnamed: LS9901.1, U9901.7
unnamed: LS9901.2, U9901.5
unnamed: LS10001.1, U10001.7
unnamed: LS10001.2, U10001.5
unnamed: LS10101.1, U10101.7
unnamed: LS10101.2, U10101.5
unnamed: LS10201.1, U10201.7
unnamed: LS10201.2, U10201.5
unnamed: LS10301.1, U10301.7
unnamed: LS10301.2, U10301.5
unnamed: LS10401.1, U10401.7
unnamed: LS10401.2, U10401.5
unnamed: LS10501.1, U10501.7
unnamed: LS10501.2, U10501.5
unnamed: PS301.4, R301.1
unnamed: R101.1, SW101.2
unnamed: R120.1, U103.2
unnamed: R120.2, R122.1, R123.1
unnamed: R121.1, U103.6
unnamed: R121.2, R126.1, R127.1
unnamed: R124.1, R125.1, U103.5
unnamed: R128.1, R129.1, U103.1
unnamed: R201.1, U201.9
unnamed: R207.1, U201.92
unnamed: R302.2, U301.5
unnamed: R303.2, U302.5
unnamed: R304.1, R305.2, R306.1
unnamed: R304.2, U301.6
unnamed: R307.2, R308.1, U302.6
unnamed: R309.2, U303.5
unnamed: R310.2, R311.1, U303.6
unnamed: R10701.2, U10701.5
unnamed: R10702.1, U10701.3
unnamed: R10801.2, U10801.5
unnamed: R10802.1, U10801.3
unnamed: R10901.2, U10901.5
unnamed: R10902.1, U10901.3
unnamed: R11001.1, U11001.9
unnamed: R11007.1, U11001.92

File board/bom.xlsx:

|  |  |  |  |  | Ordered 2020/11/29
> C101, C104, C106, C201, C203, C204, C206, C209, C210, C213-C216, C219, C220, 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 | 4.7uF | Capacitor_SMD:C_0603_1608Metric | 1276-1044-1-ND | 51 |  | 100
> C102, C103, C105, C107, C202, C205, C207, C208, C211, C212, C217, C218, C221,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 | 0.1uF | Capacitor_SMD:C_0402_1005Metric | 478-11507-1-ND | 64 |  | 130
> C301, C302 | 10uF,50V | Resistor_SMD:R_1210_3225Metric | 587-5961-1-ND | 2 |  | 4
> C304-C306, C315 | 22uF,35V | Capacitor_SMD:C_1210_3225Metric | 587-5853-1-ND | 4 |  | 10
> C311-C314, C318, C319 | 22uF | Capacitor_SMD:C_1210_3225Metric | 1276-1851-1-ND | 6 |  | 12
> C601, C701, C801, C901, C1001, C1101, C1201, C1301, C1401, C1501, C1601, C170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 | 4.7uF, 35V | Capacitor_SMD:C_1206_3216Metric | 587-3368-1-ND | 103 |  | 106
> C602, C702, C802, C902, C1002, C1102, C1202, C1302, C1402, C1502, C1602, C170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 | 0.1uF, 35V | Capacitor_SMD:C_0805_2012Metric | 587-3364-1-ND | 100 |  | 100
> C10701, C10801, C10901 | 1uF, 16V | Capacitor_SMD:C_0805_2012Metric | 587-4873-1-ND | 3 |  | 6
> D10701, D10801, D10901 | 2A, 100V | holo:DO-220A | SS2PH10-M3/84AGICT-ND | 3 |  | 6
> FB201, FB202, FB11001, FB11002 | 300R | Resistor_SMD:R_0402_1005Metric | 535-12548-1-ND | 4 |  | 10
J101 | JTAG | Connector_PinHeader_2.54mm:PinHeader_2x05_P2.54mm_Vertical_Shrouded | 732-2094-ND | 1 |  | 2
J102 | Comms | Connector_Hirose:Hirose_DF13-08P-1.25DS_1x08_P1.25mm_Horizontal | H2205-ND | 1 |  | 2
 |  |  | H2185-ND | 1 |  | 2
J301 | Power | Connector_Molex:Molex_70555_RA_1x02_P2.54 | WM14786 | 1 |  | 2
 |  |  | WM2900-ND | 1 |  | 2
> J10601-J10604 | Screw_Terminal_01x06 | Connector_Hirose:Hirose_DF13-06P-1.25DS_1x06_P1.25mm_Horizontal | H2203-ND | 4 |  | 8
 |  |  | H2183-ND | 4 |  | 8
L301 | 2.0uH | holo:NR8040 | 587-1997-1-ND | 1 |  | 2
L302 | 3.6uH | holo:NR8040 | 587-1998-1-ND | 1 |  | 2
L303 | 4.7uH | holo:NR8040 | 587-1999-1-ND | 1 |  | 2
> L10701, L10801 | 11.5uH | holo:SRR6038 | SRR6038-120YCT-ND | 2 |  | 3
L10901 | 18uH | holo:SRR6038 | SRR6038-180YCT-ND | 1 |  | -
> LS601, LS701, LS801, LS901, LS1001, LS1101, LS1201, LS1301, LS1401, LS1501, L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 | Speaker_Ultrasound | holo:MSO-P1040H07T | stock | 100 |  | -
PS301 | OKI-T36W-W40 | holo:OKI-T-36W-W40 | 811-3132-1-ND | 1 |  | 2
R101 | 330R | Resistor_SMD:R_0402_1005Metric | 541-3996-1-ND | 1 |  | 10
R103 | 1.0K | Resistor_SMD:R_0402_1005Metric | A127319CT-ND | 1 |  | 10
> R102, R104, R201-R207, R11001-R11007 | 10K | Resistor_SMD:R_0402_1005Metric | RMCF0402JT10K0CT | 16 |  | 32
R105 | 0R | Resistor_SMD:R_0402_1005Metric | ~ | 1 |  | 10
R106 | 0R | Jumper:SolderJumper-2_P1.3mm_Open_TrianglePad1.0x1.5mm | ~ | 1 |  | -
> R107-R110 | 100R | Resistor_SMD:R_0402_1005Metric | A127223CT-ND | 4 |  | 20
> R208, R11008 | 24R9 | Resistor_SMD:R_0402_1005Metric | 2037-PFR05S-24R9-FNHCT-ND | 2 |  | 10
R301 | 52R21 | Resistor_SMD:R_0603_1608Metric | RMCF0603FT26R1CT-ND | 1 |  | 10
> R302, R303, R309 | 100K | Resistor_SMD:R_0402_1005Metric | RMCS0402JT100KCT-ND | 3 |  | 10
R304 | 47K | Resistor_SMD:R_0402_1005Metric | 541-3966-1-ND | 1 |  | 10
R305 | 5.0K | Resistor_SMD:R_0402_1005Metric | 541-3972-1-ND | 1 |  | 10
R306 | 10.31K | Resistor_SMD:R_0402_1005Metric | RR12P10.2KDCT-ND | 1 |  | 2
> R307, R310 | 75K | Resistor_SMD:R_0402_1005Metric | 541-5078-1-ND | 2 |  | 10
R308 | 27.6K | Resistor_SMD:R_0402_1005Metric | CR0402-FX-27R4GLFCT-ND | 1 |  | 10
R311 | 14.46K | Resistor_SMD:R_0402_1005Metric | YAG2983CT-ND | 1 |  | 10
> R10701, R10801, R10901 | 40K | Resistor_SMD:R_0402_1005Metric | CR0402-FX-4022GLFCT-ND | 3
> R10702, R10802, R10902 | 8.9K | Resistor_SMD:R_0402_1005Metric | RMCF0402FT8K87CT-ND | 3 |  | 10
SBC401 | Raspberry_Pi_2_3 | Module:Raspberry_Pi_Zero_Socketed_THT_MountingHoles_SMT |  | 0 |  | 1
SW101 | SW_Push | Button_Switch_SMD:SW_SPST_KMR2 | CKN10246CT-ND | 0
U101 | AM26LV32CDR | Package_SO:SOIC-16_3.9x9.9mm_P1.27mm | 296-6794-1-ND | 1 |  | 2
U102 | AM26LV31 | Package_SO:SOIC-16_3.9x9.9mm_P1.27mm | 296-25912-1-ND | 1 |  | 1
> U201, U11001 | 10CL010YE144C8G | Package_QFP:EQFP-144-1EP_20x20mm_P0.5mm_EP6.7x6.7mm | 544-3578-ND | 2 |  | 2
> U202, U11002 | MIC5504-2.5YM5 | Package_TO_SOT_SMD:SOT-23-5 | 576-4880-1-ND | 2 |  | 4
> U203, U11003 | EPCQ16A | Package_SO:SOIC-8_3.9x4.9mm_P1.27mm | 544-3440-ND | 2 |  | 2
> U204, U11004 | S25FL128L | Package_SO:SOIC-8_5.275x5.275mm_P1.27mm | 428-4642-1-ND | 2 |  | 2
> U301-U303 | RT7263A | holo:SOP-EP-8_3.9x4.9mm_P1.27mm | 1028-1217-1-ND | 3 |  | 6
> U601, U701, U801, U901, U1001, U1101, U1201, U1301, U1401, U1501, U1601, U170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 | TC4428A | Package_SO:SO-8_3.9x4.9mm_P1.27mm | aliexpress | 100
> U10701, U10801, U10901 | LM3414 | Package_SO:SOIC-8-1EP_3.9x4.9mm_P1.27mm_EP2.35x2.35mm | LM3414HVMRX/NOPBCT-ND | 3 |  | 3
X101 | ASE-24.576MHz | holo:ASFL1 | ASFL1-24.576MHZ-L-T | 1 |  | 2

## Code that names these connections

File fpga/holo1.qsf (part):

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set_global_assignment -name POWER_BOARD_THERMAL_MODEL "NONE (CONSERVATIVE)"
set_location_assignment PIN_28 -to mosi
set_location_assignment PIN_24 -to sck
set_location_assignment PIN_25 -to ncs
set_location_assignment PIN_22 -to CLK_24M576
set_instance_assignment -name RESERVE_PIN AS_INPUT_TRI_STATED -to ncs
set_instance_assignment -name RESERVE_PIN AS_INPUT_TRI_STATED -to sck
set_instance_assignment -name RESERVE_PIN AS_INPUT_TRI_STATED -to mosi
set_instance_assignment -name RESERVE_PIN AS_INPUT_TRI_STATED -to CLK_24M576
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set_instance_assignment -name IO_STANDARD "3.0-V LVTTL" -to left
set_instance_assignment -name RESERVE_PIN AS_INPUT_TRI_STATED -to left
set_instance_assignment -name WEAK_PULL_UP_RESISTOR ON -to left
set_location_assignment PIN_1 -to top
set_instance_assignment -name IO_STANDARD "3.0-V LVTTL" -to top
set_instance_assignment -name RESERVE_PIN AS_INPUT_TRI_STATED -to top
set_location_assignment PIN_3 -to misc0
set_instance_assignment -name IO_STANDARD "3.0-V LVTTL" -to misc0
set_instance_assignment -name RESERVE_PIN AS_INPUT_TRI_STATED -to misc0
set_location_assignment PIN_6 -to asdo
set_instance_assignment -name IO_STANDARD "3.0-V LVTTL" -to asdo
set_location_assignment PIN_8 -to as_ncs
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set_instance_assignment -name IO_STANDARD "3.0-V LVTTL" -to as_dclk
set_location_assignment PIN_13 -to as_data0
set_instance_assignment -name IO_STANDARD "3.0-V LVTTL" -to as_data0
set_location_assignment PIN_23 -to syncin
set_instance_assignment -name IO_STANDARD "3.0-V LVTTL" -to syncin
set_location_assignment PIN_31 -to syncout
set_instance_assignment -name IO_STANDARD "3.0-V LVTTL" -to syncout
set_instance_assignment -name RESERVE_PIN AS_OUTPUT_DRIVING_AN_UNSPECIFIED_SIGNAL -to syncout
set_location_assignment PIN_32 -to miso
set_instance_assignment -name IO_STANDARD "3.0-V LVTTL" -to miso
set_instance_assignment -name RESERVE_PIN AS_INPUT_TRI_STATED -to miso
set_location_assignment PIN_43 -to f_io0
set_location_assignment PIN_44 -to f_sck
set_instance_assignment -name IO_STANDARD "3.0-V LVTTL" -to f_sck
set_location_assignment PIN_51 -to f_io3
set_instance_assignment -name IO_STANDARD "3.0-V LVTTL" -to f_io3
set_location_assignment PIN_49 -to f_ncs
set_instance_assignment -name IO_STANDARD "3.0-V LVTTL" -to f_ncs
set_instance_assignment -name RESERVE_PIN AS_OUTPUT_DRIVING_AN_UNSPECIFIED_SIGNAL -to f_ncs
set_location_assignment PIN_50 -to f_io1
set_instance_assignment -name IO_STANDARD "3.0-V LVTTL" -to f_io1
set_location_assignment PIN_141 -to misc1
set_instance_assignment -name IO_STANDARD "3.0-V LVTTL" -to misc1
set_instance_assignment -name RESERVE_PIN AS_INPUT_TRI_STATED -to misc1
set_instance_assignment -name WEAK_PULL_UP_RESISTOR ON -to misc1
set_location_assignment PIN_142 -to blue
set_instance_assignment -name IO_STANDARD "3.0-V LVTTL" -to blue
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set_global_assignment -name OUTPUT_IO_TIMING_FAR_END_VMEAS "HALF SIGNAL SWING" -rise
set_global_assignment -name OUTPUT_IO_TIMING_FAR_END_VMEAS "HALF SIGNAL SWING" -fall
set_instance_assignment -name IO_STANDARD "3.0-V LVTTL" -to f_io0
set_instance_assignment -name RESERVE_PIN AS_INPUT_TRI_STATED -to syncin
set_instance_assignment -name WEAK_PULL_UP_RESISTOR ON -to top
set_instance_assignment -name WEAK_PULL_UP_RESISTOR ON -to misc0
set_global_assignment -name ENABLE_SIGNALTAP OFF
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
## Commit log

2021-03-14 second commit
2021-03-25 updated board readme
2021-03-29 added license file
2021-05-26 remove dead code
2023-02-11 added shaders
2024-11-14 updated sim to work with Qt6.8.0
2024-11-26 corrected issue where .cu files were compiled to the root dir, failing if compiled on windows c: drive

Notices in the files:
fpga/holo1.qsf:
Copyright (C) 2019  Intel Corporation. All rights reserved.
